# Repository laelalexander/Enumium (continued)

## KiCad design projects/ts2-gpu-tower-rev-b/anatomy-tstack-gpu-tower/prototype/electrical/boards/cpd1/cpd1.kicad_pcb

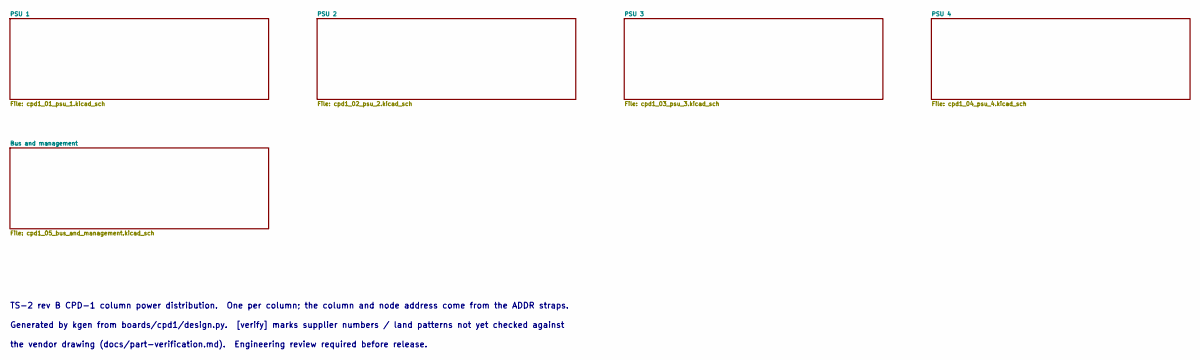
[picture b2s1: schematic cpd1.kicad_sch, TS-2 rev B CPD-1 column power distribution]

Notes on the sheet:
TS-2 rev B CPD-1 column power distribution. One per column; the column and node address come from the ADDR straps.
Generated by kgen from boards/cpd1/design.py. [verify] marks supplier numbers / land patterns not yet checked against
the vendor drawing (docs/part-verification.md). Engineering review required before release.

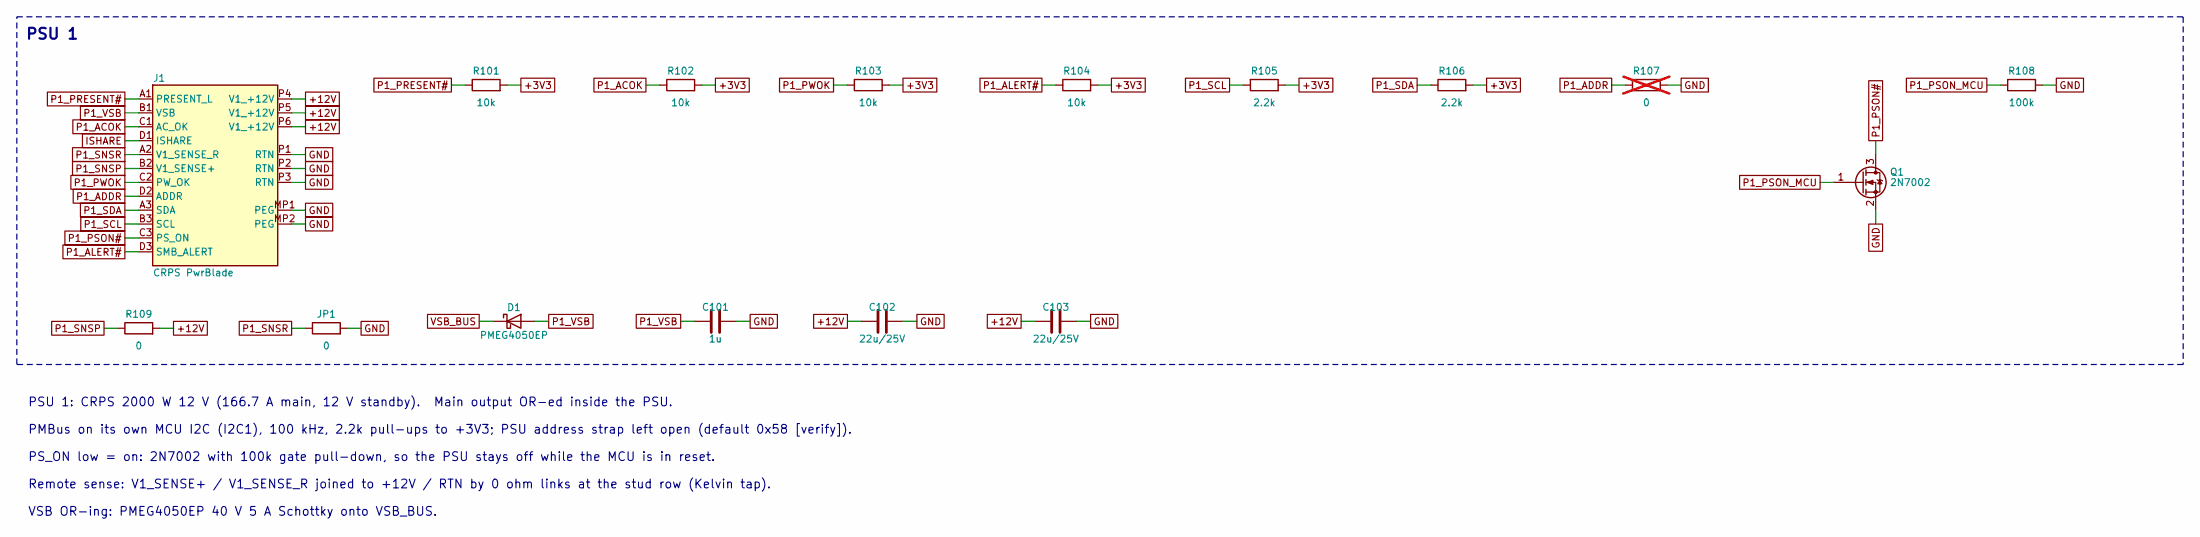
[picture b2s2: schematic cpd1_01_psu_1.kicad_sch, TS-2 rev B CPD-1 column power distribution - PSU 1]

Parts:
C101: 1u; C_0603_1608Metric; MPN CL10A105KA8NNNC; LCSC C15849
C102, C103: 22u/25V; C_1206_3216Metric; MPN CL31A226KAHNNNE; LCSC C12891
D1: PMEG4050EP; D_SOD-128; MPN PMEG4050EP,115
J1: CRPS PwrBlade; Amphenol_CRPS_PwrBlade_Vertical_PressFit; MPN 10106264-6003003LF [verify]
JP1: 0; R_0603_1608Metric; MPN 0603WAF0000T5E; LCSC C21189
Q1: 2N7002; SOT-23; MPN 2N7002,215
R101, R102, R103, R104: 10k; R_0603_1608Metric; MPN 0603WAF1002T5E; LCSC C25804
R105, R106: 2.2k; R_0603_1608Metric; MPN 0603WAF2201T5E; LCSC C4190
R107: 0; R_0603_1608Metric; MPN 0603WAF0000T5E; LCSC C21189; not fitted
R108: 100k; R_0603_1608Metric; MPN 0603WAF1003T5E; LCSC C25803
R109: 0; R_0603_1608Metric; MPN 0603WAF0000T5E; LCSC C21189

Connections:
+3V3: R101.2, R102.2, R103.2, R104.2, R105.2, R106.2; also elsewhere on the board
+12V: C102.1, C103.1, J1.P4 (V1_+12V), J1.P5 (V1_+12V), J1.P6 (V1_+12V), R109.2; also elsewhere on the board
GND: C101.2, C102.2, C103.2, J1.MP1 (PEG), J1.MP2 (PEG), J1.P1 (RTN), J1.P2 (RTN), J1.P3 (RTN), JP1.2, Q1.2 (S), R107.2, R108.2; also elsewhere on the board
ISHARE: J1.D1 (ISHARE); also elsewhere on the board
P1_ACOK: J1.C1 (AC_OK), R102.1; also elsewhere on the board
P1_ADDR: J1.D2 (ADDR), R107.1
P1_ALERT#: J1.D3 (SMB_ALERT), R104.1; also elsewhere on the board
P1_PRESENT#: J1.A1 (PRESENT_L), R101.1; also elsewhere on the board
P1_PSON#: J1.C3 (PS_ON), Q1.3 (D)
P1_PSON_MCU: Q1.1 (G), R108.1; also elsewhere on the board
P1_PWOK: J1.C2 (PW_OK), R103.1; also elsewhere on the board
P1_SCL: J1.B3 (SCL), R105.1; also elsewhere on the board
P1_SDA: J1.A3 (SDA), R106.1; also elsewhere on the board
P1_SNSP: J1.B2 (V1_SENSE+), R109.1
P1_SNSR: J1.A2 (V1_SENSE_R), JP1.1
P1_VSB: C101.1, D1.2 (A), J1.B1 (VSB)
VSB_BUS: D1.1 (K); also elsewhere on the board

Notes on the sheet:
PSU 1
PSU 1: CRPS 2000 W 12 V (166.7 A main, 12 V standby). Main output OR-ed inside the PSU.
PMBus on its own MCU I2C (I2C1), 100 kHz, 2.2k pull-ups to +3V3; PSU address strap left open (default 0x58 [verify]).
PS_ON low = on: 2N7002 with 100k gate pull-down, so the PSU stays off while the MCU is in reset.
Remote sense: V1_SENSE+ / V1_SENSE_R joined to +12V / RTN by 0 ohm links at the stud row (Kelvin tap).
VSB OR-ing: PMEG4050EP 40 V 5 A Schottky onto VSB_BUS.

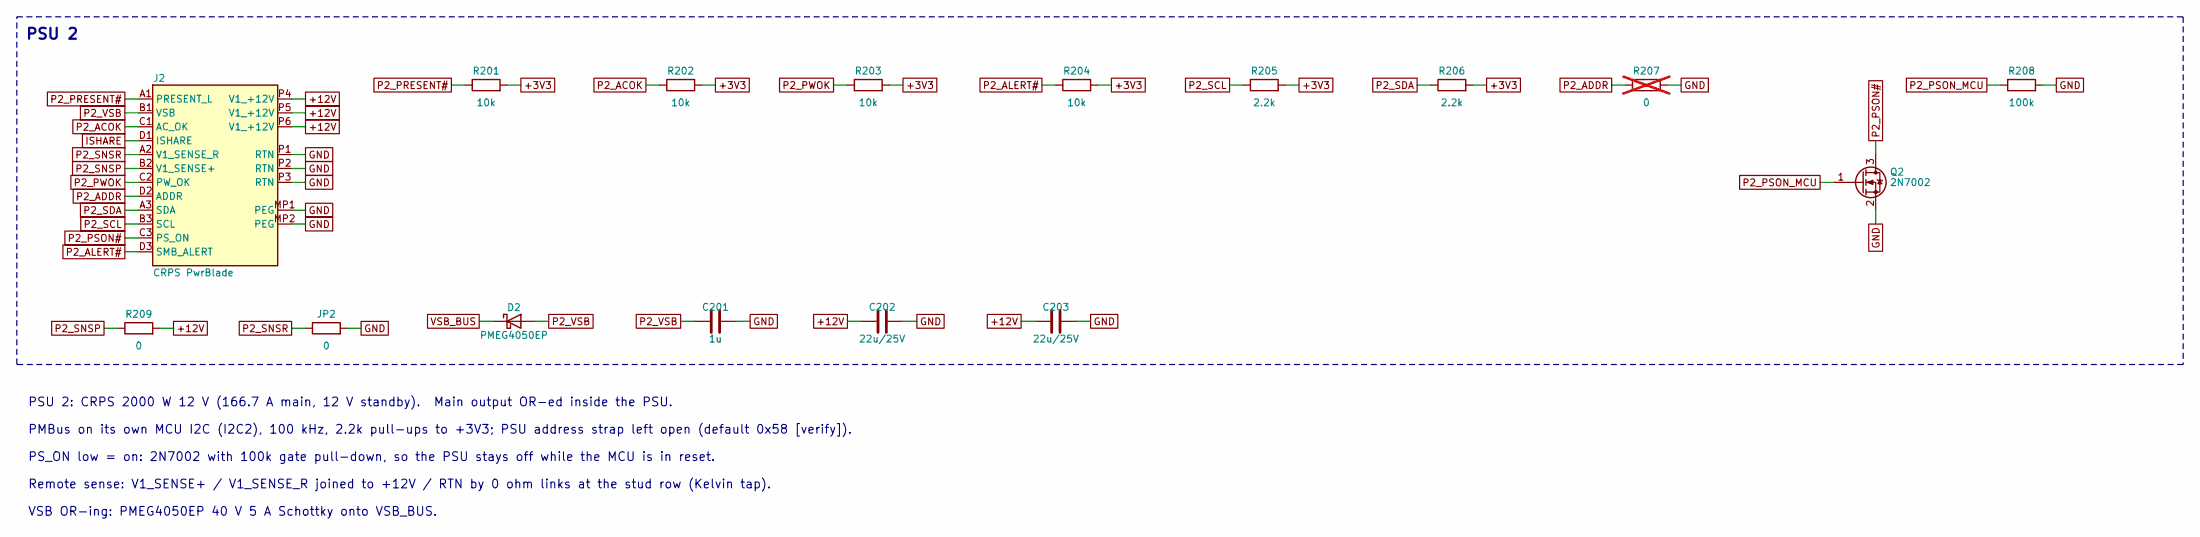
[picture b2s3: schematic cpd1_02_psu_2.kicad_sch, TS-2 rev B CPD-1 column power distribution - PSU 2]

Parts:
C201: 1u; C_0603_1608Metric; MPN CL10A105KA8NNNC; LCSC C15849
C202, C203: 22u/25V; C_1206_3216Metric; MPN CL31A226KAHNNNE; LCSC C12891
D2: PMEG4050EP; D_SOD-128; MPN PMEG4050EP,115
J2: CRPS PwrBlade; Amphenol_CRPS_PwrBlade_Vertical_PressFit; MPN 10106264-6003003LF [verify]
JP2: 0; R_0603_1608Metric; MPN 0603WAF0000T5E; LCSC C21189
Q2: 2N7002; SOT-23; MPN 2N7002,215
R201, R202, R203, R204: 10k; R_0603_1608Metric; MPN 0603WAF1002T5E; LCSC C25804
R205, R206: 2.2k; R_0603_1608Metric; MPN 0603WAF2201T5E; LCSC C4190
R207: 0; R_0603_1608Metric; MPN 0603WAF0000T5E; LCSC C21189; not fitted
R208: 100k; R_0603_1608Metric; MPN 0603WAF1003T5E; LCSC C25803
R209: 0; R_0603_1608Metric; MPN 0603WAF0000T5E; LCSC C21189

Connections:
+3V3: R201.2, R202.2, R203.2, R204.2, R205.2, R206.2; also elsewhere on the board
+12V: C202.1, C203.1, J2.P4 (V1_+12V), J2.P5 (V1_+12V), J2.P6 (V1_+12V), R209.2; also elsewhere on the board
GND: C201.2, C202.2, C203.2, J2.MP1 (PEG), J2.MP2 (PEG), J2.P1 (RTN), J2.P2 (RTN), J2.P3 (RTN), JP2.2, Q2.2 (S), R207.2, R208.2; also elsewhere on the board
ISHARE: J2.D1 (ISHARE); also elsewhere on the board
P2_ACOK: J2.C1 (AC_OK), R202.1; also elsewhere on the board
P2_ADDR: J2.D2 (ADDR), R207.1
P2_ALERT#: J2.D3 (SMB_ALERT), R204.1; also elsewhere on the board
P2_PRESENT#: J2.A1 (PRESENT_L), R201.1; also elsewhere on the board
P2_PSON#: J2.C3 (PS_ON), Q2.3 (D)
P2_PSON_MCU: Q2.1 (G), R208.1; also elsewhere on the board
P2_PWOK: J2.C2 (PW_OK), R203.1; also elsewhere on the board
P2_SCL: J2.B3 (SCL), R205.1; also elsewhere on the board
P2_SDA: J2.A3 (SDA), R206.1; also elsewhere on the board
P2_SNSP: J2.B2 (V1_SENSE+), R209.1
P2_SNSR: J2.A2 (V1_SENSE_R), JP2.1
P2_VSB: C201.1, D2.2 (A), J2.B1 (VSB)
VSB_BUS: D2.1 (K); also elsewhere on the board

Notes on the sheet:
PSU 2
PSU 2: CRPS 2000 W 12 V (166.7 A main, 12 V standby). Main output OR-ed inside the PSU.
PMBus on its own MCU I2C (I2C2), 100 kHz, 2.2k pull-ups to +3V3; PSU address strap left open (default 0x58 [verify]).
PS_ON low = on: 2N7002 with 100k gate pull-down, so the PSU stays off while the MCU is in reset.
Remote sense: V1_SENSE+ / V1_SENSE_R joined to +12V / RTN by 0 ohm links at the stud row (Kelvin tap).
VSB OR-ing: PMEG4050EP 40 V 5 A Schottky onto VSB_BUS.

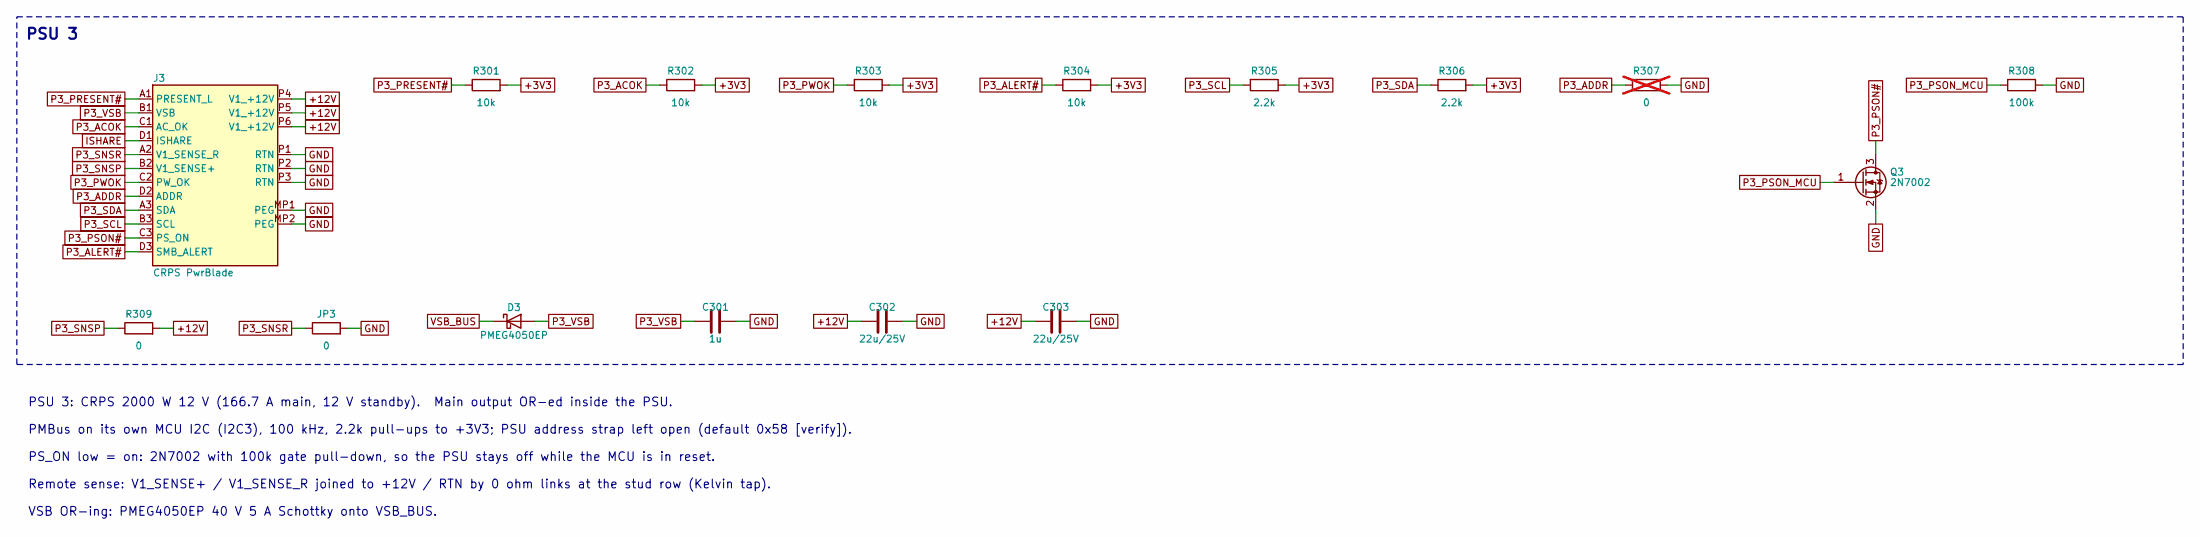
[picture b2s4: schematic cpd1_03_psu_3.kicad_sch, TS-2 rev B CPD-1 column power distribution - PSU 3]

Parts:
C301: 1u; C_0603_1608Metric; MPN CL10A105KA8NNNC; LCSC C15849
C302, C303: 22u/25V; C_1206_3216Metric; MPN CL31A226KAHNNNE; LCSC C12891
D3: PMEG4050EP; D_SOD-128; MPN PMEG4050EP,115
J3: CRPS PwrBlade; Amphenol_CRPS_PwrBlade_Vertical_PressFit; MPN 10106264-6003003LF [verify]
JP3: 0; R_0603_1608Metric; MPN 0603WAF0000T5E; LCSC C21189
Q3: 2N7002; SOT-23; MPN 2N7002,215
R301, R302, R303, R304: 10k; R_0603_1608Metric; MPN 0603WAF1002T5E; LCSC C25804
R305, R306: 2.2k; R_0603_1608Metric; MPN 0603WAF2201T5E; LCSC C4190
R307: 0; R_0603_1608Metric; MPN 0603WAF0000T5E; LCSC C21189; not fitted
R308: 100k; R_0603_1608Metric; MPN 0603WAF1003T5E; LCSC C25803
R309: 0; R_0603_1608Metric; MPN 0603WAF0000T5E; LCSC C21189

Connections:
+3V3: R301.2, R302.2, R303.2, R304.2, R305.2, R306.2; also elsewhere on the board
+12V: C302.1, C303.1, J3.P4 (V1_+12V), J3.P5 (V1_+12V), J3.P6 (V1_+12V), R309.2; also elsewhere on the board
GND: C301.2, C302.2, C303.2, J3.MP1 (PEG), J3.MP2 (PEG), J3.P1 (RTN), J3.P2 (RTN), J3.P3 (RTN), JP3.2, Q3.2 (S), R307.2, R308.2; also elsewhere on the board
ISHARE: J3.D1 (ISHARE); also elsewhere on the board
P3_ACOK: J3.C1 (AC_OK), R302.1; also elsewhere on the board
P3_ADDR: J3.D2 (ADDR), R307.1
P3_ALERT#: J3.D3 (SMB_ALERT), R304.1; also elsewhere on the board
P3_PRESENT#: J3.A1 (PRESENT_L), R301.1; also elsewhere on the board
P3_PSON#: J3.C3 (PS_ON), Q3.3 (D)
P3_PSON_MCU: Q3.1 (G), R308.1; also elsewhere on the board
P3_PWOK: J3.C2 (PW_OK), R303.1; also elsewhere on the board
P3_SCL: J3.B3 (SCL), R305.1; also elsewhere on the board
P3_SDA: J3.A3 (SDA), R306.1; also elsewhere on the board
P3_SNSP: J3.B2 (V1_SENSE+), R309.1
P3_SNSR: J3.A2 (V1_SENSE_R), JP3.1
P3_VSB: C301.1, D3.2 (A), J3.B1 (VSB)
VSB_BUS: D3.1 (K); also elsewhere on the board

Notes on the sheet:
PSU 3
PSU 3: CRPS 2000 W 12 V (166.7 A main, 12 V standby). Main output OR-ed inside the PSU.
PMBus on its own MCU I2C (I2C3), 100 kHz, 2.2k pull-ups to +3V3; PSU address strap left open (default 0x58 [verify]).
PS_ON low = on: 2N7002 with 100k gate pull-down, so the PSU stays off while the MCU is in reset.
Remote sense: V1_SENSE+ / V1_SENSE_R joined to +12V / RTN by 0 ohm links at the stud row (Kelvin tap).
VSB OR-ing: PMEG4050EP 40 V 5 A Schottky onto VSB_BUS.

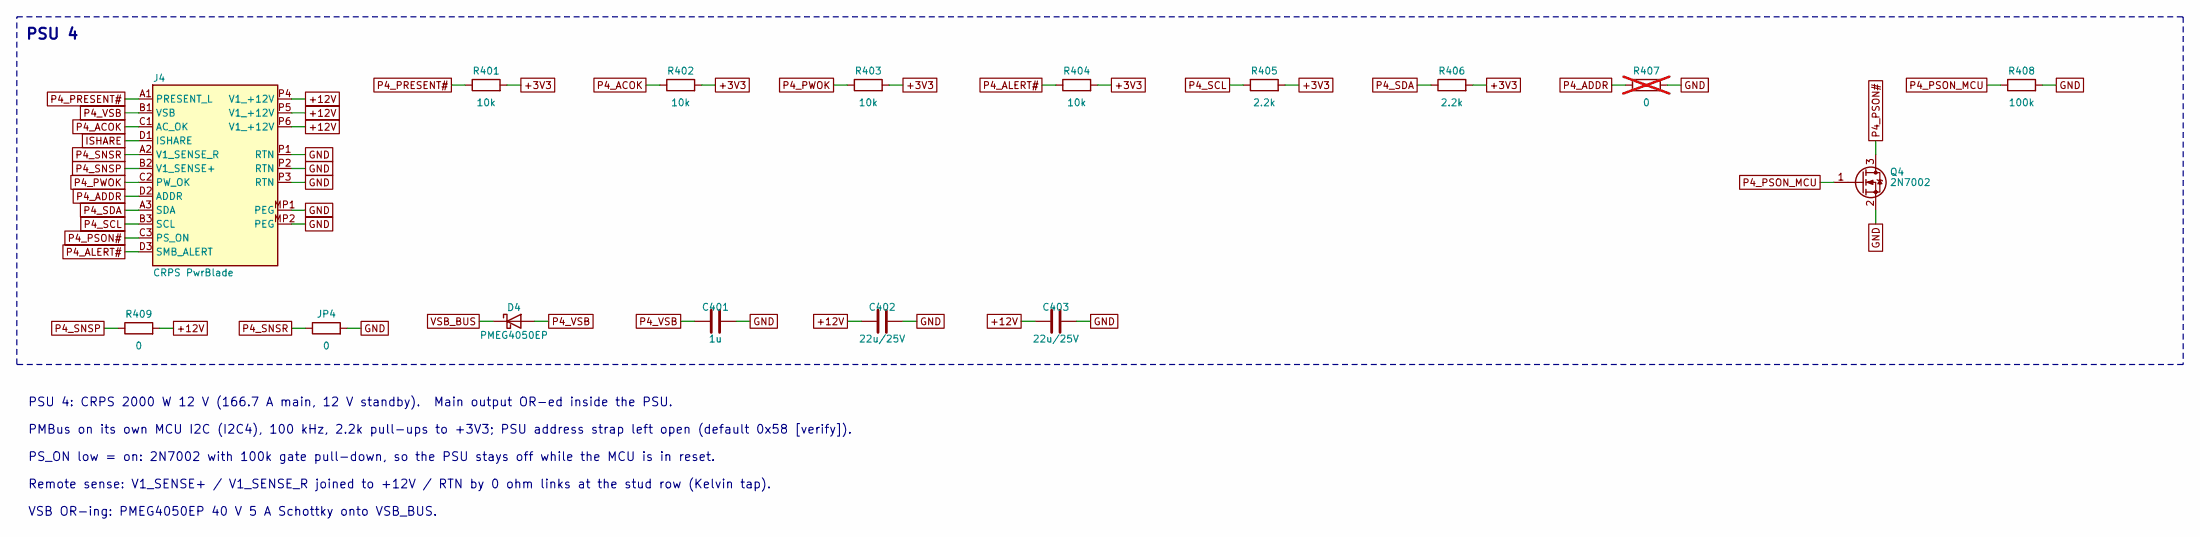
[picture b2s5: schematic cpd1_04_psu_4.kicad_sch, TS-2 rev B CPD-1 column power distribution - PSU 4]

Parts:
C401: 1u; C_0603_1608Metric; MPN CL10A105KA8NNNC; LCSC C15849
C402, C403: 22u/25V; C_1206_3216Metric; MPN CL31A226KAHNNNE; LCSC C12891
D4: PMEG4050EP; D_SOD-128; MPN PMEG4050EP,115
J4: CRPS PwrBlade; Amphenol_CRPS_PwrBlade_Vertical_PressFit; MPN 10106264-6003003LF [verify]
JP4: 0; R_0603_1608Metric; MPN 0603WAF0000T5E; LCSC C21189
Q4: 2N7002; SOT-23; MPN 2N7002,215
R401, R402, R403, R404: 10k; R_0603_1608Metric; MPN 0603WAF1002T5E; LCSC C25804
R405, R406: 2.2k; R_0603_1608Metric; MPN 0603WAF2201T5E; LCSC C4190
R407: 0; R_0603_1608Metric; MPN 0603WAF0000T5E; LCSC C21189; not fitted
R408: 100k; R_0603_1608Metric; MPN 0603WAF1003T5E; LCSC C25803
R409: 0; R_0603_1608Metric; MPN 0603WAF0000T5E; LCSC C21189

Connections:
+3V3: R401.2, R402.2, R403.2, R404.2, R405.2, R406.2; also elsewhere on the board
+12V: C402.1, C403.1, J4.P4 (V1_+12V), J4.P5 (V1_+12V), J4.P6 (V1_+12V), R409.2; also elsewhere on the board
GND: C401.2, C402.2, C403.2, J4.MP1 (PEG), J4.MP2 (PEG), J4.P1 (RTN), J4.P2 (RTN), J4.P3 (RTN), JP4.2, Q4.2 (S), R407.2, R408.2; also elsewhere on the board
ISHARE: J4.D1 (ISHARE); also elsewhere on the board
P4_ACOK: J4.C1 (AC_OK), R402.1; also elsewhere on the board
P4_ADDR: J4.D2 (ADDR), R407.1
P4_ALERT#: J4.D3 (SMB_ALERT), R404.1; also elsewhere on the board
P4_PRESENT#: J4.A1 (PRESENT_L), R401.1; also elsewhere on the board
P4_PSON#: J4.C3 (PS_ON), Q4.3 (D)
P4_PSON_MCU: Q4.1 (G), R408.1; also elsewhere on the board
P4_PWOK: J4.C2 (PW_OK), R403.1; also elsewhere on the board
P4_SCL: J4.B3 (SCL), R405.1; also elsewhere on the board
P4_SDA: J4.A3 (SDA), R406.1; also elsewhere on the board
P4_SNSP: J4.B2 (V1_SENSE+), R409.1
P4_SNSR: J4.A2 (V1_SENSE_R), JP4.1
P4_VSB: C401.1, D4.2 (A), J4.B1 (VSB)
VSB_BUS: D4.1 (K); also elsewhere on the board

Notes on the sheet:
PSU 4
PSU 4: CRPS 2000 W 12 V (166.7 A main, 12 V standby). Main output OR-ed inside the PSU.
PMBus on its own MCU I2C (I2C4), 100 kHz, 2.2k pull-ups to +3V3; PSU address strap left open (default 0x58 [verify]).
PS_ON low = on: 2N7002 with 100k gate pull-down, so the PSU stays off while the MCU is in reset.
Remote sense: V1_SENSE+ / V1_SENSE_R joined to +12V / RTN by 0 ohm links at the stud row (Kelvin tap).
VSB OR-ing: PMEG4050EP 40 V 5 A Schottky onto VSB_BUS.

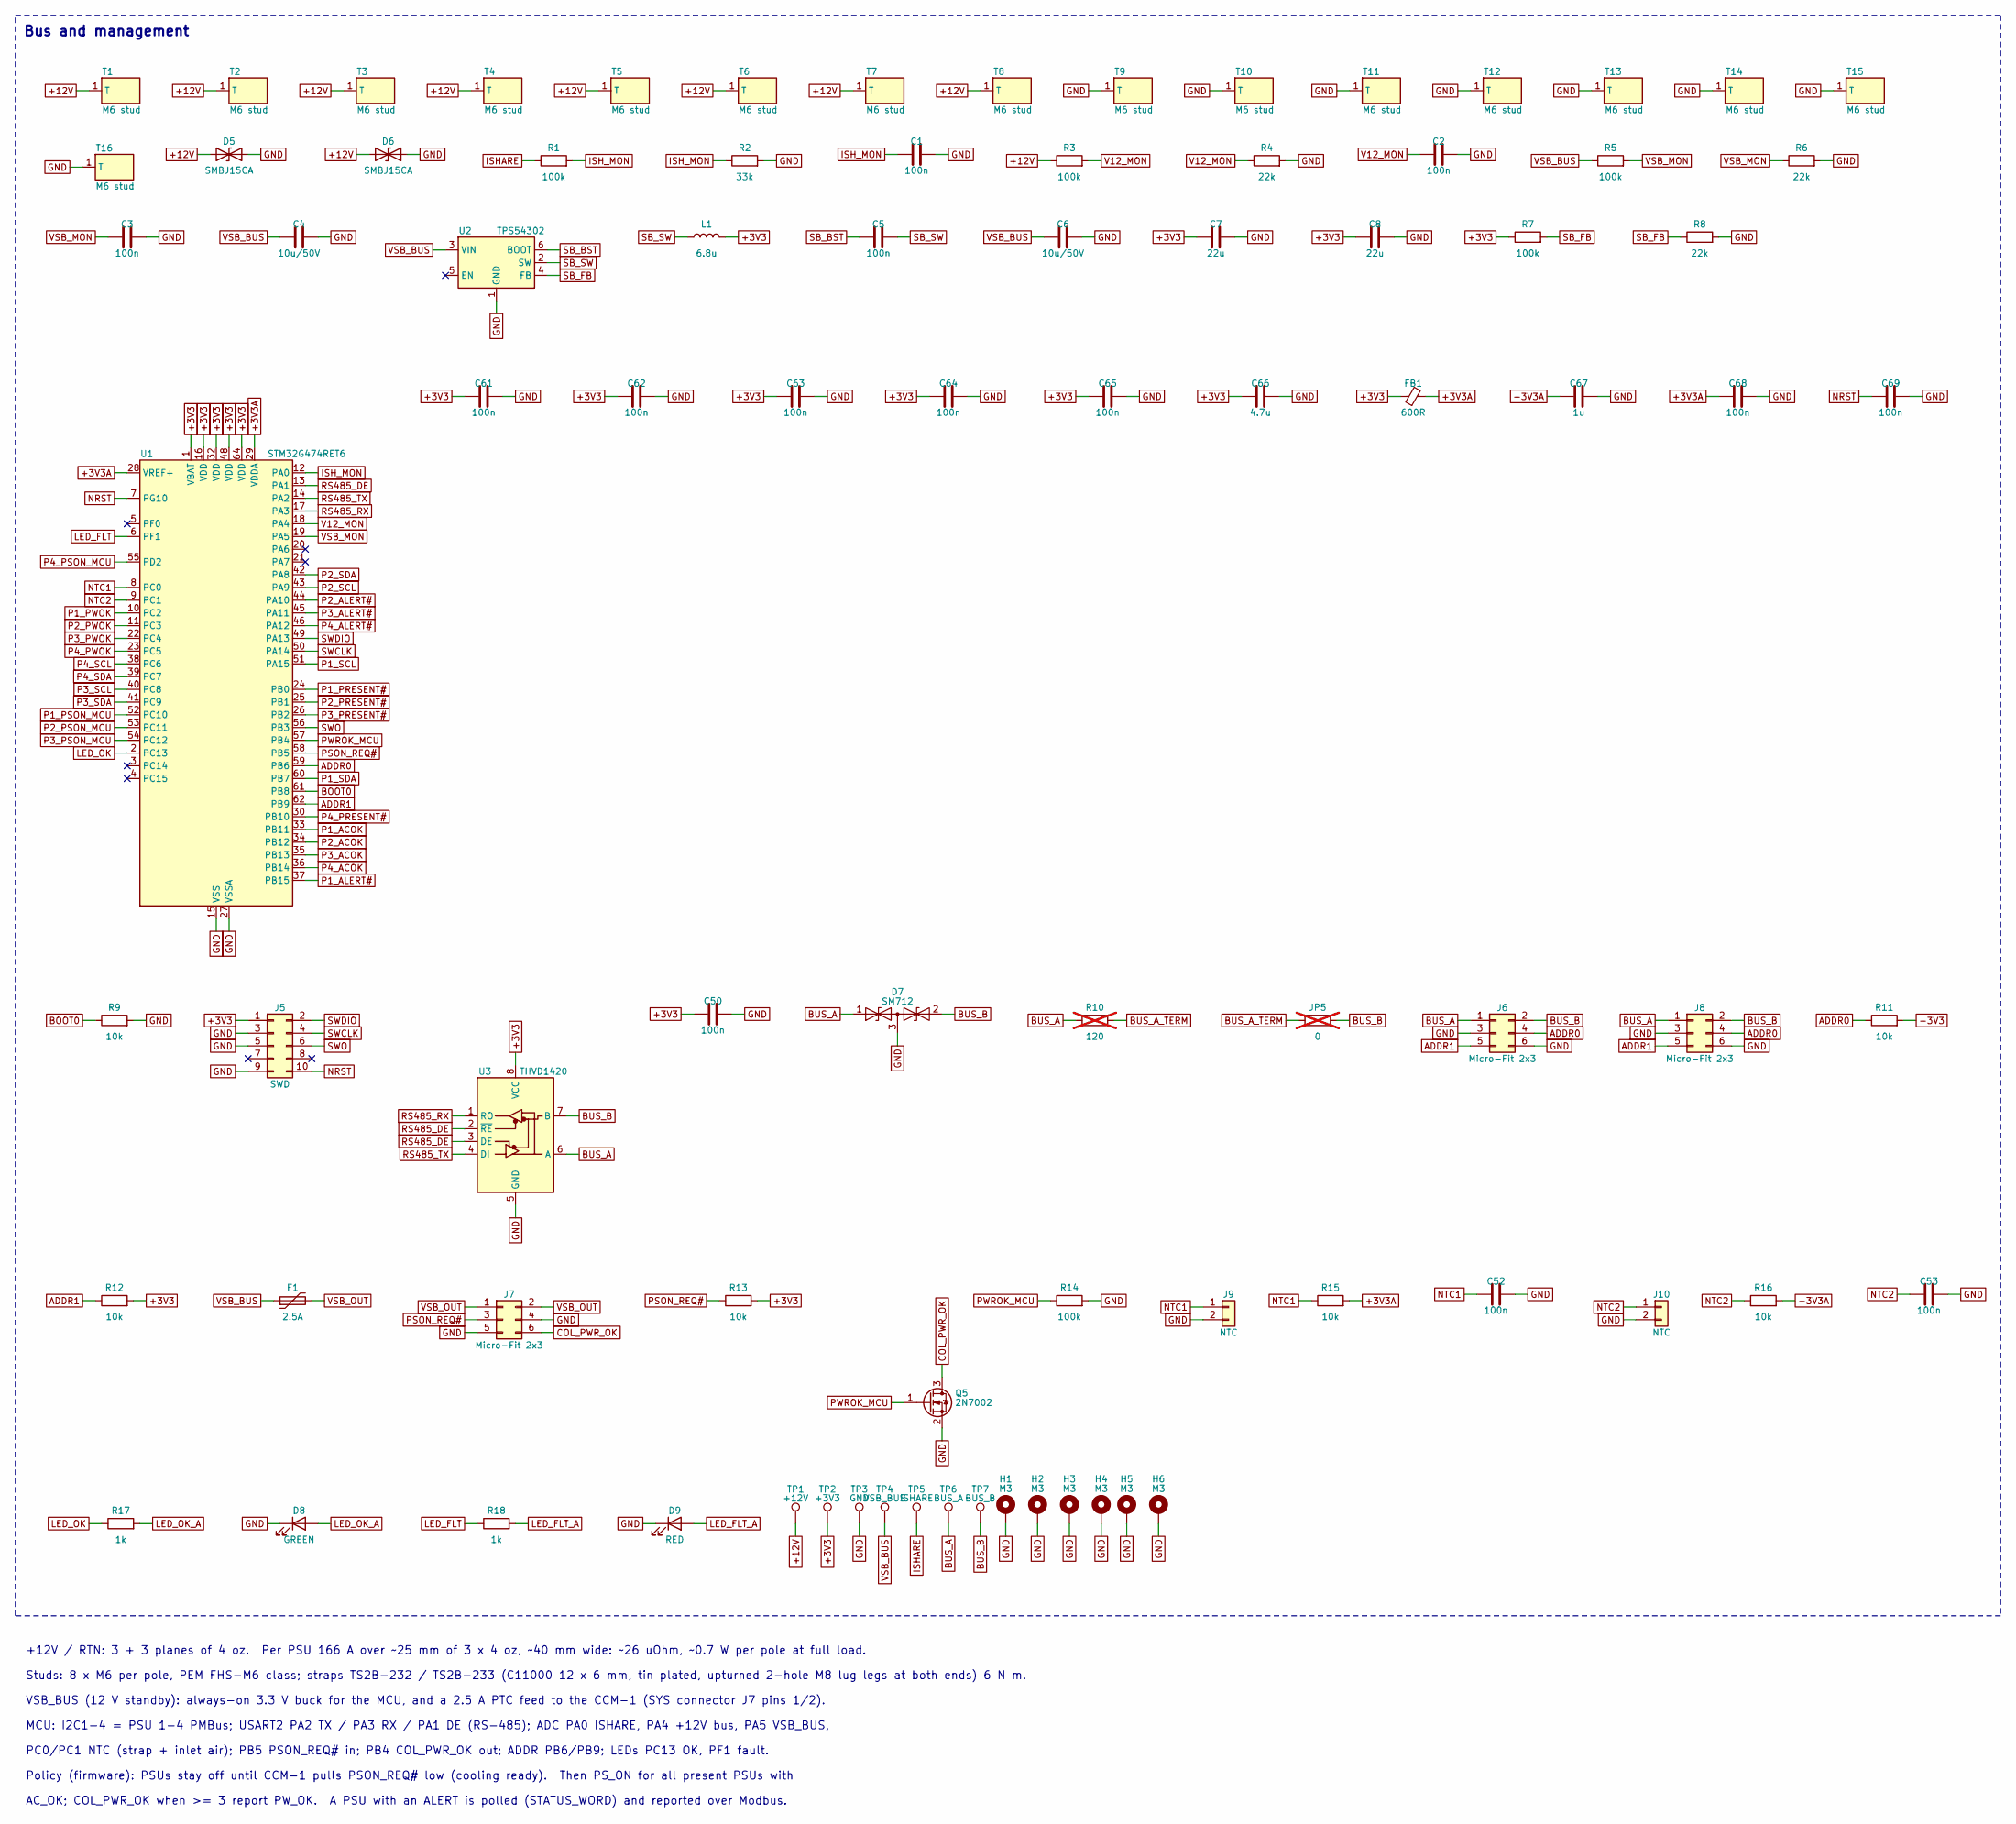
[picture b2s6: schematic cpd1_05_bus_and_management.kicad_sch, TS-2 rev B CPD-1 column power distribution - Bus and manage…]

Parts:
C1, C2, C3, C5, C50, C52, C53, C61, C62, C63, C64, C65, C68, C69: 100n; C_0603_1608Metric; MPN CL10B104KB8NNNC; LCSC C1591
C4, C6: 10u/50V; C_1206_3216Metric; MPN GRM31CR61H106KA12L; LCSC C13585
C7, C8: 22u; C_0805_2012Metric; MPN CL21A226MAQNNNE; LCSC C45783
C66: 4.7u; C_0603_1608Metric; MPN CL10A475KO8NNNC; LCSC C19666
C67: 1u; C_0603_1608Metric; MPN CL10A105KA8NNNC; LCSC C15849
D5, D6: SMBJ15CA; D_SMB; MPN SMBJ15CA
D7: SM712; SOT-23; MPN SM712.TCT
D8: GREEN; LED_0603_1608Metric; MPN 150060VS75000
D9: RED; LED_0603_1608Metric; MPN 150060RS75000
F1: 2.5A; Fuse_1812_4532Metric; MPN MF-MSMF250/16X-2
FB1: 600R; L_0603_1608Metric; MPN BLM18KG601SN1D
H1, H2, H3, H4, H5, H6: M3; MountingHole_3.2mm_M3_Pad_Via
J5: SWD; PinHeader_2x05_P1.27mm_Vertical; MPN FTSH-105-01-F-DV-K
J6, J7, J8: Micro-Fit 2x3; Molex_Micro-Fit_3.0_43045-0612_2x03_P3.00mm_Vertical; MPN 43045-0612
J9, J10: NTC; JST_PH_B2B-PH-K_1x02_P2.00mm_Vertical; MPN B2B-PH-K-S
JP5: 0; R_0603_1608Metric; MPN 0603WAF0000T5E; not fitted
L1: 6.8u; L_Bourns_SRP7028A_7.3x6.6mm; MPN SRP7028A-6R8M
Q5: 2N7002; SOT-23; MPN 2N7002,215
R1, R3, R5, R7, R14: 100k; R_0603_1608Metric; MPN 0603WAF1003T5E; LCSC C25803
R2: 33k; R_0603_1608Metric; MPN 0603WAF3302T5E; LCSC C4216
R4, R6, R8: 22k; R_0603_1608Metric; MPN 0603WAF2202T5E; LCSC C31850
R9, R11, R12, R13, R15, R16: 10k; R_0603_1608Metric; MPN 0603WAF1002T5E; LCSC C25804
R10: 120; R_0603_1608Metric; MPN 0603WAF1200T5E; LCSC C22787; not fitted
R17, R18: 1k; R_0603_1608Metric; MPN 0603WAF1001T5E; LCSC C21190
T1, T2, T3, T4, T5, T6, T7, T8, T9, T10, T11, T12, T13, T14, T15, T16: M6 stud; Power_Stud_M6_PressFit; MPN FHS-M6-20ZI [verify]
TP1: +12V; TestPoint_Pad_D1.5mm
TP2: +3V3; TestPoint_Pad_D1.5mm
TP3: GND; TestPoint_Pad_D1.5mm
TP4: VSB_BUS; TestPoint_Pad_D1.5mm
TP5: ISHARE; TestPoint_Pad_D1.5mm
TP6: BUS_A; TestPoint_Pad_D1.5mm
TP7: BUS_B; TestPoint_Pad_D1.5mm
U1: STM32G474RET6; LQFP-64_10x10mm_P0.5mm; MPN STM32G474RET6
U2: TPS54302; SOT-23-6; MPN TPS54302DDCR
U3: THVD1420; SOIC-8_3.9x4.9mm_P1.27mm; MPN THVD1420DR

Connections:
+3V3: C7.1, C8.1, C50.1, C61.1, C62.1, C63.1, C64.1, C65.1, C66.1, FB1.1, J5.1, L1.2, R7.1, R11.2, R12.2, R13.2, TP2.1, U1.1 (VBAT), U1.16 (VDD), U1.32 (VDD), U1.48 (VDD), U1.64 (VDD), U3.8 (VCC); also elsewhere on the board
+3V3A: C67.1, C68.1, FB1.2, R15.2, R16.2, U1.28 (VREF+), U1.29 (VDDA)
+12V: D5.1 (A1), D6.1 (A1), R3.1, T1.1, T2.1, T3.1, T4.1, T5.1, T6.1, T7.1, T8.1, TP1.1; also elsewhere on the board
ADDR0: J6.4, J8.4, R11.1, U1.59 (PB6)
ADDR1: J6.5, J8.5, R12.1, U1.62 (PB9)
BOOT0: R9.1, U1.61 (PB8)
BUS_A: D7.1 (A1), J6.1, J8.1, R10.1, TP6.1, U3.6 (A)
BUS_A_TERM: JP5.1, R10.2
BUS_B: D7.2 (A2), J6.2, J8.2, JP5.2, TP7.1, U3.7 (B)
COL_PWR_OK: J7.6, Q5.3 (D)
GND: C1.2, C2.2, C3.2, C4.2, C6.2, C7.2, C8.2, C50.2, C52.2, C53.2, C61.2, C62.2, C63.2, C64.2, C65.2, C66.2, C67.2, C68.2, C69.2, D5.2 (A2), D6.2 (A2), D7.3 (common), D8.1 (K), D9.1 (K), H1.1, H2.1, H3.1, H4.1, H5.1, H6.1, J5.3, J5.5, J5.9, J6.3, J6.6, J7.4, J7.5, J8.3, J8.6, J9.2, J10.2, Q5.2 (S), R2.2, R4.2, R6.2, R8.2, R9.2, R14.2, T9.1, T10.1, T11.1, T12.1, T13.1, T14.1, T15.1, T16.1, TP3.1, U1.15 (VSS), U1.27 (VSSA), U1.31 (VSS), U1.47 (VSS), U1.63 (VSS), U2.1 (GND), U3.5 (GND); also elsewhere on the board
ISHARE: R1.1, TP5.1; also elsewhere on the board
ISH_MON: C1.1, R1.2, R2.1, U1.12 (PA0)
LED_FLT: R18.1, U1.6 (PF1)
LED_FLT_A: D9.2 (A), R18.2
LED_OK: R17.1, U1.2 (PC13)
LED_OK_A: D8.2 (A), R17.2
NRST: C69.1, J5.10, U1.7 (PG10)
NTC1: C52.1, J9.1, R15.1, U1.8 (PC0)
NTC2: C53.1, J10.1, R16.1, U1.9 (PC1)
P1_ACOK: U1.33 (PB11); also elsewhere on the board
P1_ALERT#: U1.37 (PB15); also elsewhere on the board
P1_PRESENT#: U1.24 (PB0); also elsewhere on the board
P1_PSON_MCU: U1.52 (PC10); also elsewhere on the board
P1_PWOK: U1.10 (PC2); also elsewhere on the board
P1_SCL: U1.51 (PA15); also elsewhere on the board
P1_SDA: U1.60 (PB7); also elsewhere on the board
P2_ACOK: U1.34 (PB12); also elsewhere on the board
P2_ALERT#: U1.44 (PA10); also elsewhere on the board
P2_PRESENT#: U1.25 (PB1); also elsewhere on the board
P2_PSON_MCU: U1.53 (PC11); also elsewhere on the board
P2_PWOK: U1.11 (PC3); also elsewhere on the board
P2_SCL: U1.43 (PA9); also elsewhere on the board
P2_SDA: U1.42 (PA8); also elsewhere on the board
P3_ACOK: U1.35 (PB13); also elsewhere on the board
P3_ALERT#: U1.45 (PA11); also elsewhere on the board
P3_PRESENT#: U1.26 (PB2); also elsewhere on the board
P3_PSON_MCU: U1.54 (PC12); also elsewhere on the board
P3_PWOK: U1.22 (PC4); also elsewhere on the board
P3_SCL: U1.40 (PC8); also elsewhere on the board
P3_SDA: U1.41 (PC9); also elsewhere on the board
P4_ACOK: U1.36 (PB14); also elsewhere on the board
P4_ALERT#: U1.46 (PA12); also elsewhere on the board
P4_PRESENT#: U1.30 (PB10); also elsewhere on the board
P4_PSON_MCU: U1.55 (PD2); also elsewhere on the board
P4_PWOK: U1.23 (PC5); also elsewhere on the board
P4_SCL: U1.38 (PC6); also elsewhere on the board
P4_SDA: U1.39 (PC7); also elsewhere on the board
PSON_REQ#: J7.3, R13.1, U1.58 (PB5)
PWROK_MCU: Q5.1 (G), R14.1, U1.57 (PB4)
RS485_DE: U1.13 (PA1), U3.2 (~RE), U3.3 (DE)
RS485_RX: U1.17 (PA3), U3.1 (RO)
RS485_TX: U1.14 (PA2), U3.4 (DI)
SB_BST: C5.1, U2.6 (BOOT)
SB_FB: R7.2, R8.1, U2.4 (FB)
SB_SW: C5.2, L1.1, U2.2 (SW)
SWCLK: J5.4, U1.50 (PA14)
SWDIO: J5.2, U1.49 (PA13)
SWO: J5.6, U1.56 (PB3)
V12_MON: C2.1, R3.2, R4.1, U1.18 (PA4)
VSB_BUS: C4.1, C6.1, F1.1, R5.1, TP4.1, U2.3 (VIN); also elsewhere on the board
VSB_MON: C3.1, R5.2, R6.1, U1.19 (PA5)
VSB_OUT: F1.2, J7.1, J7.2

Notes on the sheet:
Bus and management
+12V / RTN: 3 + 3 planes of 4 oz. Per PSU 166 A over ~25 mm of 3 x 4 oz, ~40 mm wide: ~26 uOhm, ~0.7 W per pole at full load.
Studs: 8 x M6 per pole, PEM FHS-M6 class; straps TS2B-232 / TS2B-233 (C11000 12 x 6 mm, tin plated, upturned 2-hole M8 lug legs at both ends) 6 N m.
VSB_BUS (12 V standby): always-on 3.3 V buck for the MCU, and a 2.5 A PTC feed to the CCM-1 (SYS connector J7 pins 1/2).
MCU: I2C1-4 = PSU 1-4 PMBus; USART2 PA2 TX / PA3 RX / PA1 DE (RS-485); ADC PA0 ISHARE, PA4 +12V bus, PA5 VSB_BUS,
PC0/PC1 NTC (strap + inlet air); PB5 PSON_REQ# in; PB4 COL_PWR_OK out; ADDR PB6/PB9; LEDs PC13 OK, PF1 fault.
Policy (firmware): PSUs stay off until CCM-1 pulls PSON_REQ# low (cooling ready). Then PS_ON for all present PSUs with
AC_OK; COL_PWR_OK when >= 3 report PW_OK. A PSU with an ALERT is polled (STATUS_WORD) and reported over Modbus.
